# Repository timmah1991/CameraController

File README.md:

# CameraController

There are four components to this project:

*Board Schematics/Layout (autodesk EAGLE)

*Enclosure STEP and STL files (Fusion 360)

*Sample Particle Xenon Firmware (Particle IDE)
-firmware will expose two functions through the particle cloud, shutter1 and shutter2. Each function must be called with a string as an argument. That argument is the amount of time to activate the shutter for, in milliseconds. 

*Example NodeRED Workflow and integration (Particle Dev Console)
The flow included will allow you to create a slack channel for triggering the camera shutter. It will look for the word photograph, photo, pic, etc, and a designation for which camera you are asking it to take a picture with; c1, c2, both. It will send a confirmation message back to you after shooting the picture. 

This project is the cumulative effort of the handful of engineering skills that I've been trying to develop over the last few weeks. I think the project came out nicely, after a few bumps in the road with circuit design and layout.

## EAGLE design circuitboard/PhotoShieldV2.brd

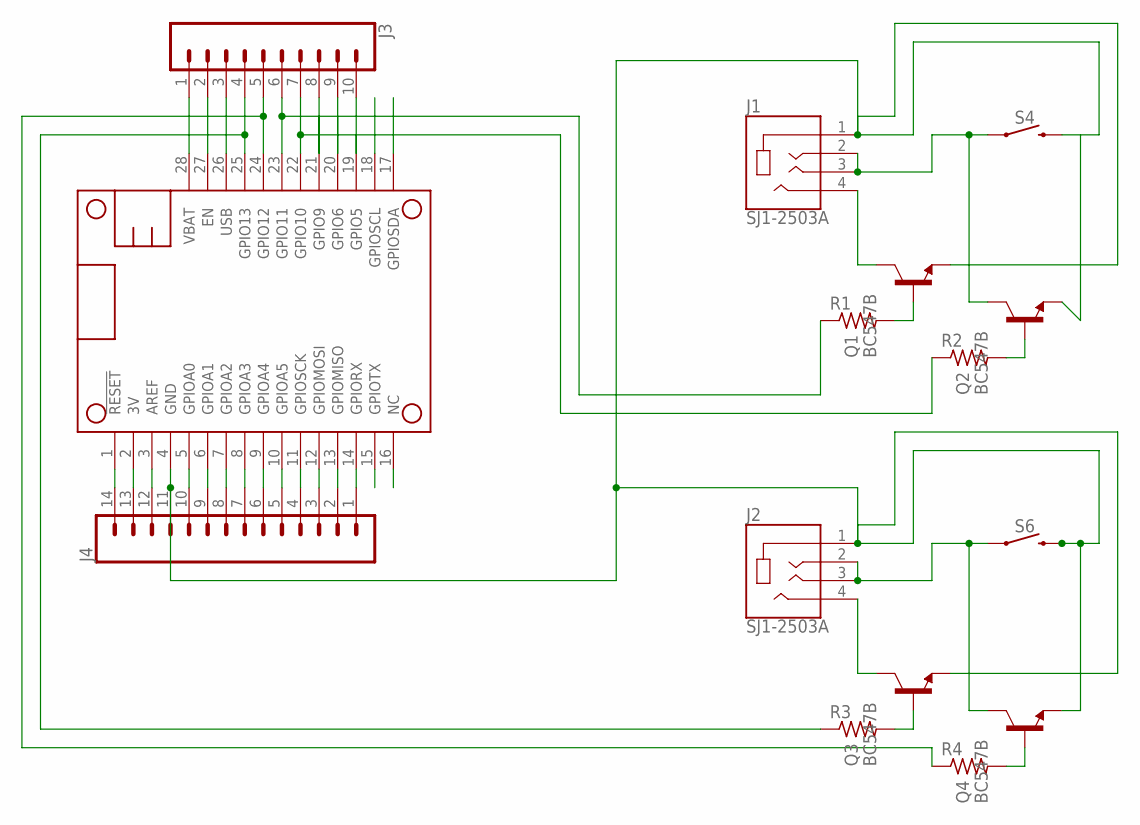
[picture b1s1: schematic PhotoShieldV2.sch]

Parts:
J1, J2: SJ1-2503A; CUI_SJ1-2503A
J3: CONN_10"; 1X10
J4: CONN_14; 1X14
MS1: FEATHERWING
Q1, Q2, Q3, Q4: BC547B; TO92
R1, R2, R3, R4: R-US_R0805; R0805
S4, S6: MOMENTARY-SWITCH-SPST-SMD-4.6X2.8MM; TACTILE_SWITCH_SMD_4.6X2.8MM

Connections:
3V: J4.13, MS1.2 (3V)
unnamed: J3.7, MS1.22 (GPIO10), R2.1
unnamed: J1.4, Q1.3 (C)
unnamed: J1.2, J1.3, Q2.3 (C), S4.1, S4.2 (1)
unnamed: Q2.2 (B), R2.2
unnamed: J3.2, MS1.27 (EN)
unnamed: Q1.2 (B), R1.2
unnamed: J2.4, Q3.3 (C)
unnamed: J1.1, J2.1, J4.11, MS1.4 (GND), Q1.1 (E), Q2.1 (E), Q3.1 (E), Q4.1 (E), S4.3 (2), S4.4 (2), S6.3 (2), S6.4 (2)
unnamed: J2.2, J2.3, Q4.3 (C), S6.1, S6.2 (1)
unnamed: J3.4, MS1.25 (GPIO13), R3.1
unnamed: Q4.2 (B), R4.2
unnamed: J3.5, MS1.24 (GPIO12), R4.1
unnamed: Q3.2 (B), R3.2
unnamed: J4.14, MS1.1 (!RESET)
unnamed: J4.12, MS1.3 (AREF)
unnamed: J4.10, MS1.5 (GPIOA0)
unnamed: J4.9, MS1.6 (GPIOA1)
unnamed: J4.8, MS1.7 (GPIOA2)
unnamed: J4.7, MS1.8 (GPIOA3)
unnamed: J4.6, MS1.9 (GPIOA4)
unnamed: J4.5, MS1.10 (GPIOA5)
unnamed: J4.4, MS1.11 (GPIOSCK)
unnamed: J4.3, MS1.12 (GPIOMOSI)
unnamed: J4.2, MS1.13 (GPIOMISO)
unnamed: J4.1, MS1.14 (GPIORX)
unnamed: J3.6, MS1.23 (GPIO11), R1.1
unnamed: J3.8, MS1.21 (GPIO9)
unnamed: J3.9, MS1.20 (GPIO6)
unnamed: J3.10, MS1.19 (GPIO5)
USB: J3.3, MS1.26 (USB)
VBAT: J3.1, MS1.28 (VBAT)

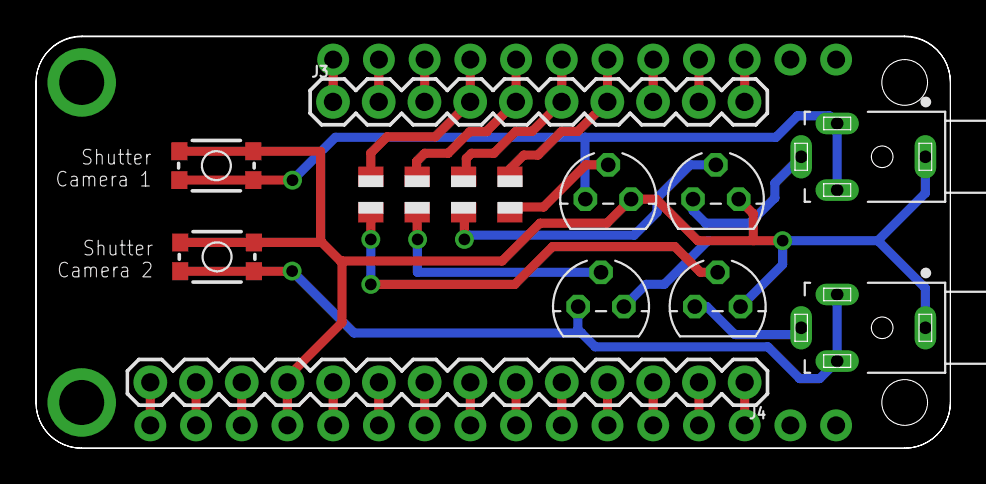
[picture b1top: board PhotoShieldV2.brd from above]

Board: 2 copper layers, 50.8 x 22.9 mm, 15 parts (0 on the bottom side), 32 nets.

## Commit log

2019-01-11 changed readme formatting
2019-01-11 Added circuit board schematics
2019-01-11 deleting DS store garbage
2019-01-11 adding unfinished firmware
2019-01-11 finished firmware
2019-01-11 fixed some typos
2019-01-11 added enclosure STL's
2019-01-11 added nodeRed flow
2019-01-11 added nodered screenshot
2019-01-11 added pictures
2019-02-19 .DS_Store banished
2019-02-19 Added the eclipse capture that was augmented by this project

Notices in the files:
parts and their libraries:
SparkFun-Switches: Licensing: Creative Commons ShareAlike 4.0 International - https://creativecommons.org/licenses/by-sa/4.0
